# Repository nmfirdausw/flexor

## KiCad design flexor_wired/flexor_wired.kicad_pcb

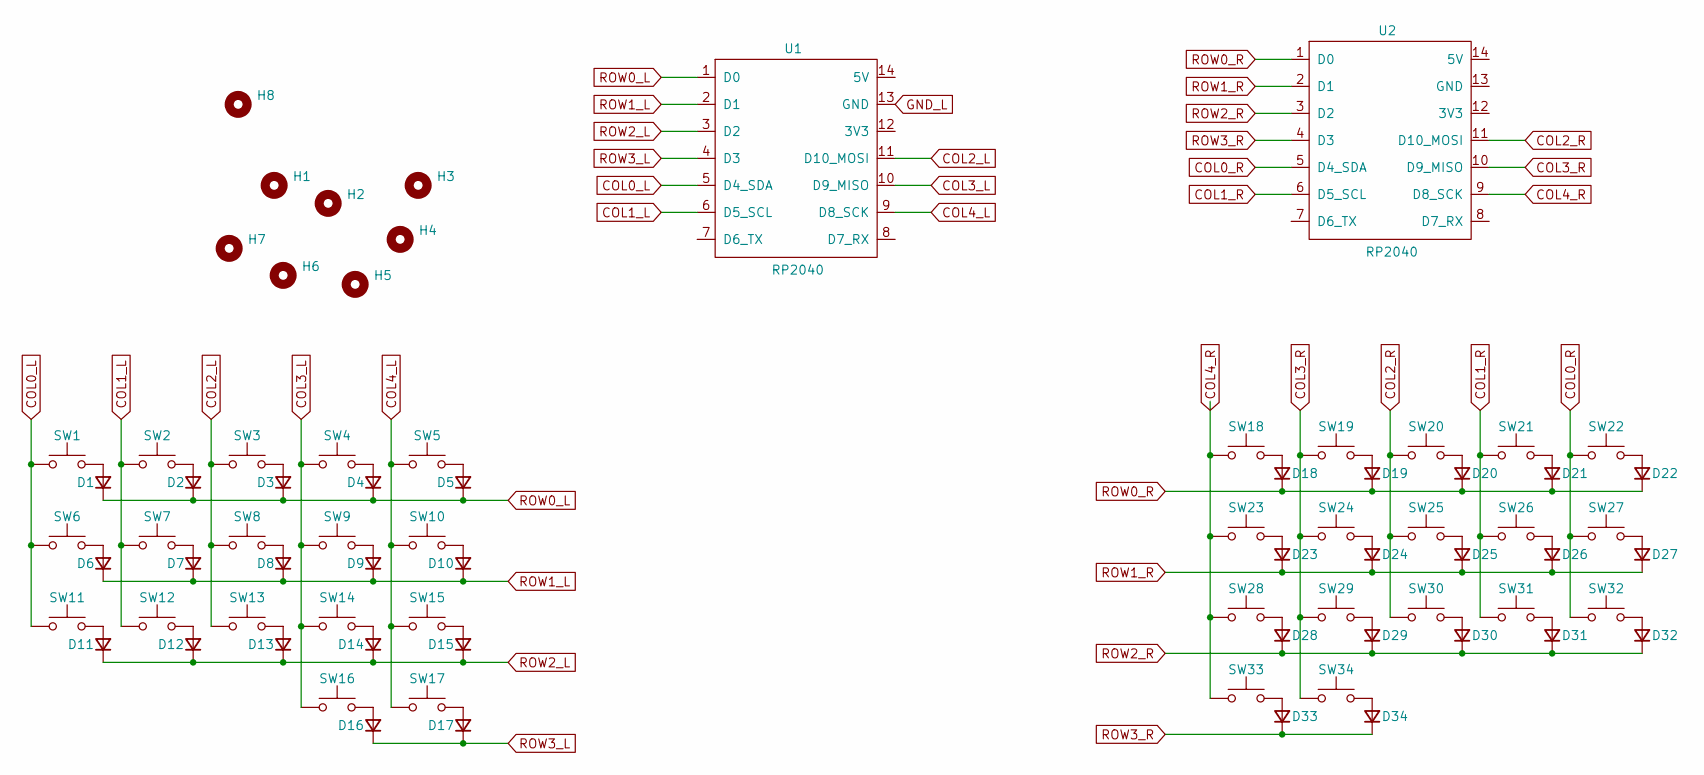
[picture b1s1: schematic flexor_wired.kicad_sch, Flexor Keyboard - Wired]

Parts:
D1, D2, D3, D4, D5, D6, D7, D8, D9, D10, D11, D12, D13, D14, D15, D16, D17, D18, D19, D20, D21, D22, D23, D24, D25, D26, D27, D28, D29, D30, D31, D32, D33, D34: 1N4148W; 1N4148W_SOD-123_SMD
H1, H2, H3, H4, H5, H6, H7, H8: MountingHole; 3.2mm_M3_DIN965_Pad
SW1, SW2, SW3, SW4, SW5, SW6, SW7, SW8, SW9, SW10, SW11, SW12, SW13, SW14, SW15, SW16, SW17, SW18, SW19, SW20, SW21, SW22, SW23, SW24, SW25, SW26, SW27, SW28, SW29, SW30, SW31, SW32, SW33, SW34: PG1350; PG1350_Choc_V1
U1, U2: RP2040; XIAO_RP2040_SMD

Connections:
COL0_L: SW1.1, SW6.1, SW11.1, U1.5 (D4_SDA)
COL0_R: SW22.1, SW27.1, SW32.1, U2.5 (D4_SDA)
COL1_L: SW2.1, SW7.1, SW12.1, U1.6 (D5_SCL)
COL1_R: SW21.1, SW26.1, SW31.1, U2.6 (D5_SCL)
COL2_L: SW3.1, SW8.1, SW13.1, U1.11 (D10_MOSI)
COL2_R: SW20.1, SW25.1, SW30.1, U2.11 (D10_MOSI)
COL3_L: SW4.1, SW9.1, SW14.1, SW16.1, U1.10 (D9_MISO)
COL3_R: SW19.1, SW24.1, SW29.1, SW34.1, U2.10 (D9_MISO)
COL4_L: SW5.1, SW10.1, SW15.1, SW17.1, U1.9 (D8_SCK)
COL4_R: SW18.1, SW23.1, SW28.1, SW33.1, U2.9 (D8_SCK)
GND_L: U1.13 (GND)
unnamed: D1.2 (A), SW1.2
unnamed: D2.2 (A), SW2.2
unnamed: D3.2 (A), SW3.2
unnamed: D4.2 (A), SW4.2
unnamed: D5.2 (A), SW5.2
unnamed: D6.2 (A), SW6.2
unnamed: D7.2 (A), SW7.2
unnamed: D8.2 (A), SW8.2
unnamed: D9.2 (A), SW9.2
unnamed: D10.2 (A), SW10.2
unnamed: D11.2 (A), SW11.2
unnamed: D12.2 (A), SW12.2
unnamed: D13.2 (A), SW13.2
unnamed: D14.2 (A), SW14.2
unnamed: D15.2 (A), SW15.2
unnamed: D16.2 (A), SW16.2
unnamed: D17.2 (A), SW17.2
unnamed: D18.2 (A), SW18.2
unnamed: D19.2 (A), SW19.2
unnamed: D20.2 (A), SW20.2
unnamed: D21.2 (A), SW21.2
unnamed: D22.2 (A), SW22.2
unnamed: D23.2 (A), SW23.2
unnamed: D24.2 (A), SW24.2
unnamed: D25.2 (A), SW25.2
unnamed: D26.2 (A), SW26.2
unnamed: D27.2 (A), SW27.2
unnamed: D28.2 (A), SW28.2
unnamed: D29.2 (A), SW29.2
unnamed: D30.2 (A), SW30.2
unnamed: D31.2 (A), SW31.2
unnamed: D32.2 (A), SW32.2
unnamed: D33.2 (A), SW33.2
unnamed: D34.2 (A), SW34.2
ROW0_L: D1.1 (K), D2.1 (K), D3.1 (K), D4.1 (K), D5.1 (K), U1.1 (D0)
ROW0_R: D18.1 (K), D19.1 (K), D20.1 (K), D21.1 (K), D22.1 (K), U2.1 (D0)
ROW1_L: D6.1 (K), D7.1 (K), D8.1 (K), D9.1 (K), D10.1 (K), U1.2 (D1)
ROW1_R: D23.1 (K), D24.1 (K), D25.1 (K), D26.1 (K), D27.1 (K), U2.2 (D1)
ROW2_L: D11.1 (K), D12.1 (K), D13.1 (K), D14.1 (K), D15.1 (K), U1.3 (D2)
ROW2_R: D28.1 (K), D29.1 (K), D30.1 (K), D31.1 (K), D32.1 (K), U2.3 (D2)
ROW3_L: D16.1 (K), D17.1 (K), U1.4 (D3)
ROW3_R: D33.1 (K), D34.1 (K), U2.4 (D3)

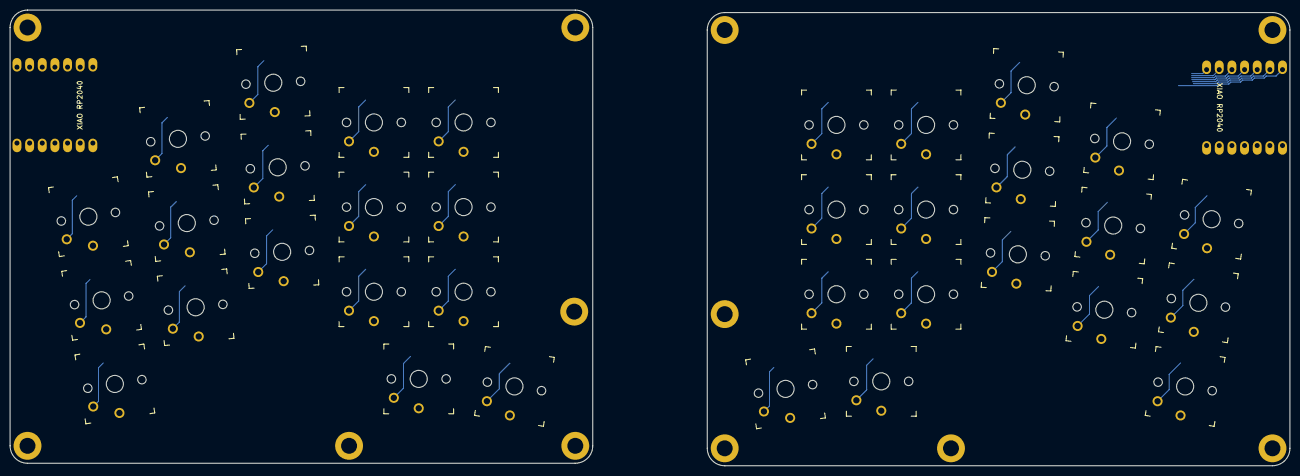
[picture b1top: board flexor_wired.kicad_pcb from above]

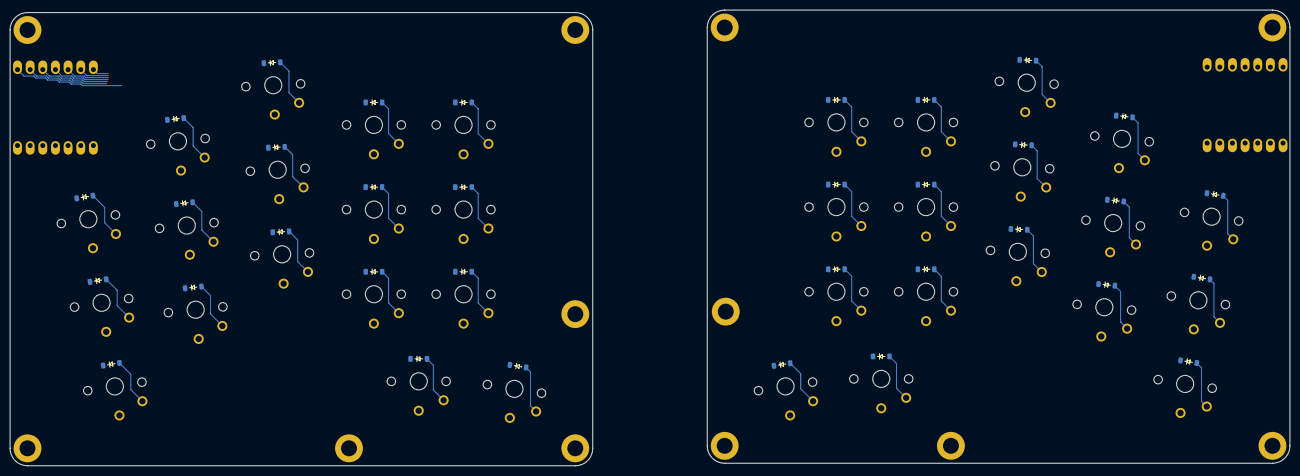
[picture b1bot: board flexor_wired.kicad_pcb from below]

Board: 2 copper layers, 257.0 x 91.5 mm, 82 parts (34 on the bottom side), 52 nets.

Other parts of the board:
H9, H10, H11, H12: MountingHole; 3.2mm_M3_DIN965_Pad

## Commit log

2025-08-14 feat: initialize flexor keyboard project with wired and wireless variants
    - Add KiCad project files for flexor_wired variant
    - Add KiCad project files for flexor_wireless variant
    - Include PCB, schematic, project, and preference files for both variants
2025-08-14 chore: add .gitignore to exclude backup folders and macOS system files
    - Ignore flexor_wired-backups and flexor_wireless-backups directories
    - Ignore .DS_Store files in root and all subdirectories
2025-08-14 feat: add project metadata to KiCad files
    - Add comments, revision, title and issue date to schematic and PCB
    - Update project information for flexor_wired variant
    - Update project information for flexor_wireless variant
2025-08-14 feat: add Kailh Choc V1 switch components
    - Add 3D models for hotswap socket and switch
    - Add KiCad footprints for standard and hotswap variants
    - Support both soldered and hotswappable Choc V1 switches
2025-08-14 refactor: prioritize wired version development
    - Remove flexor_wireless project files to focus on wired implementation first
    - Add footprint info cache for flexor_wired variant
    - Wireless version will be developed after wired version is complete
2025-08-14 feat: add Seeed Studio XIAO components and update naming
    - Add 3D models for XIAO RP2040 and nRF52840 variants
    - Add KiCad footprints for XIAO microcontrollers
    - Add XIAO symbol library for schematic use
    - Rename Kailh footprints with simplified naming (remove Kailh_ prefix)
    - Update schematic and footprint cache
2025-08-15 feat: add 1N4148W diode components and improve XIAO model naming
    - Add new 1N4148W SOD123 diode 3D model
    - Add corresponding KiCad footprint for 1N4148W SOD123 package
    - Rename XIAO 3D models to include '_MCU' suffix for clarity:
    * Seeed_Studio_XIAO_RP2040_SMD.step → Seeed_Studio_XIAO_RP2040_SMD_MCU.step
    * Seeed_Studio_XIAO_nRF52840_SMD.step → Seeed_Studio_XIAO_nRF52840_SMD_MCU.step
2025-08-25 feat: update PCB design and project configuration
    - Update flexor_wired PCB layout and schematic
    - Update project configuration and preferences
    - Update footprint info cache
2025-08-25 feat: add KiCad library tables
    - Add footprint library table (fp-lib-table)
    - Add symbol library table (sym-lib-table)
2025-08-25 refactor: update diode footprint and 3D model
    - Replace 1N4148W_SOD123 with 1N4148W_SOD-123_SMD footprint
    - Remove old SOD123 diode 3D model
    - Use standardized SOD-123 SMD naming convention
2025-08-25 feat: update Kailh Choc switch footprints
    - Update PG1350_Choc_V1 standard footprint
    - Update PG1350_Choc_V1_hotswap footprint
    - Improve switch mounting and pad layouts
2025-08-25 feat: update Seeed XIAO microcontroller footprints
    - Update XIAO_RP2040_SMD footprint
    - Update XIAO_nRF52840_SMD footprint
    - Improve pad layouts and mounting specifications
2025-08-25 feat: add comprehensive 3D model collection
    - Add 1N4148W SOD-123 diode 3D model
    - Add Kailh Choc keycap variants:
    - FunkMonk 1u keycap
    - MBK keycap
    - Mote angled (up/down/left/right) keycaps
    - Mote flat and homing keycaps
2025-08-25 feat: add mounting hole footprint library
    - Add Mounting_Hole.pretty footprint library
    - Support PCB mounting and assembly requirements
2025-09-02 feat(pcb): implement keycap layout with stagger and splay for both sides
2025-09-02 feat(schematic): update schematic to support new keycap layout
2025-09-02 feat(footprints): update Kailh switch, diode, and XIAO RP2040 footprints
2025-09-02 refactor(3d-models): remove old Kailh Choc keycap 3D models
2025-09-02 feat(3d-models): add new keycap 3D models for KLP Lame, MBK, and Mote variants
2025-09-02 chore: update project configuration and add new footprint variants
